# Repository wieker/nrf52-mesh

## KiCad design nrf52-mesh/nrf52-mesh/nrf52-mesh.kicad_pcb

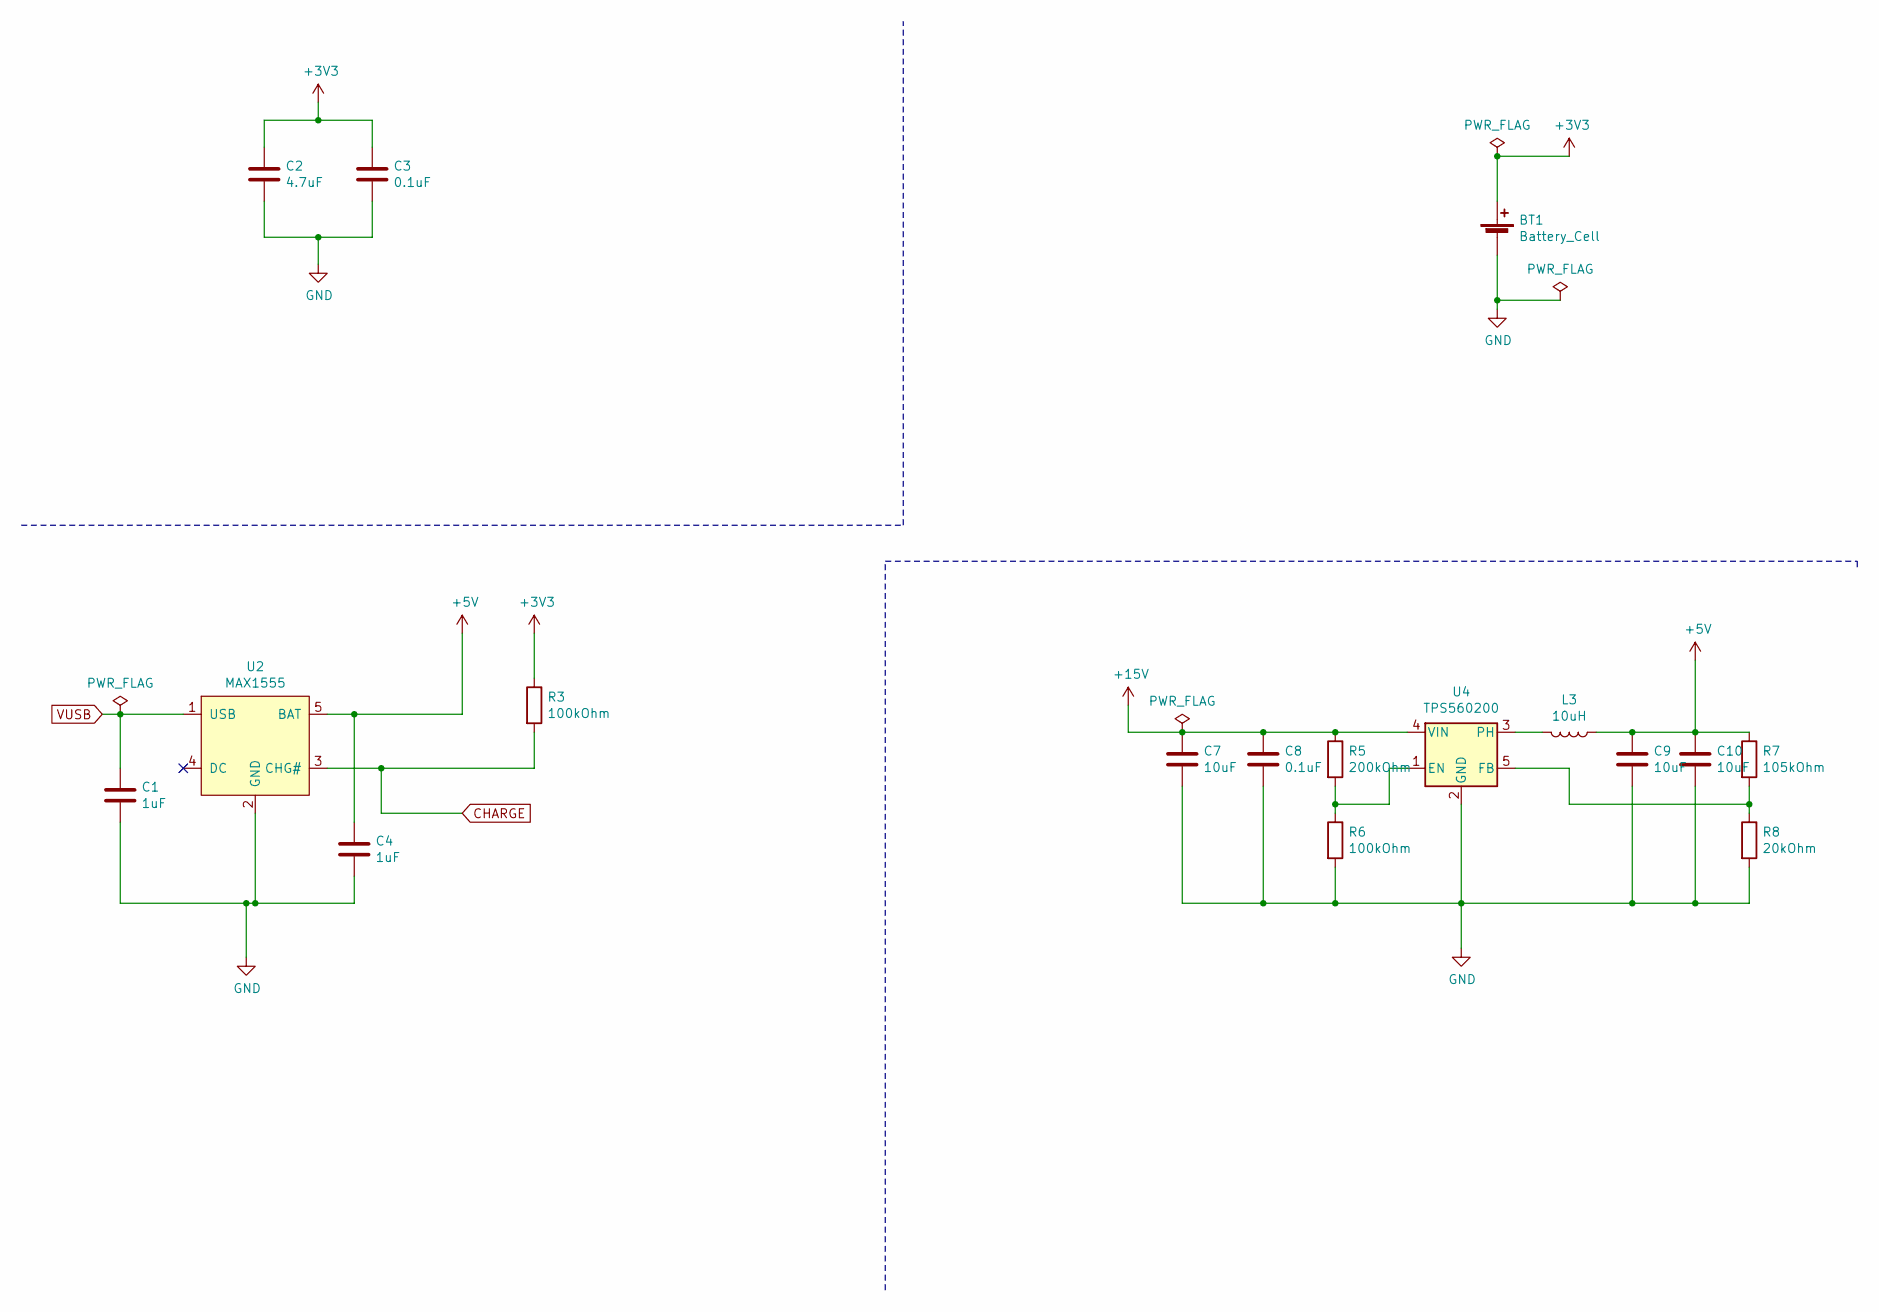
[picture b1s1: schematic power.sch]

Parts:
BT1: Battery_Cell; CR2032
C1, C4: 1uF; C_0402_1005Metric
C2: 4.7uF; C_0402_1005Metric
C3, C8: 0.1uF; C_0402_1005Metric
C7, C9, C10: 10uF; C_0603_1608Metric
L3: 10uH; L_0805_2012Metric
R3, R6: 100kOhm; R_0402_1005Metric
R5: 200kOhm; R_0402_1005Metric
R7: 105kOhm; R_0402_1005Metric
R8: 20kOhm; R_0402_1005Metric
U2: MAX1555; SOT-23-5
U4: TPS560200; SOT-23-5

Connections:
+3V3: BT1.1 (+), C2.1, C3.1, R3.1; also elsewhere on the board
+5V: C4.2, C9.1, C10.1, L3.1, R7.1, U2.5 (BAT); also elsewhere on the board
+15V: C7.1, C8.1, R5.1, U4.4 (VIN); also elsewhere on the board
CHARGE: R3.2, U2.3 (CHG#); also elsewhere on the board
GND: BT1.2 (-), C1.2, C2.2, C3.2, C4.1, C7.2, C8.2, C9.2, C10.2, R6.2, R8.2, U2.2 (GND), U4.2 (GND); also elsewhere on the board
unnamed: L3.2, U4.3 (PH)
unnamed: R5.2, R6.1, U4.1 (EN)
unnamed: R7.2, R8.1, U4.5 (FB)
VUSB: C1.1, U2.1 (USB); also elsewhere on the board

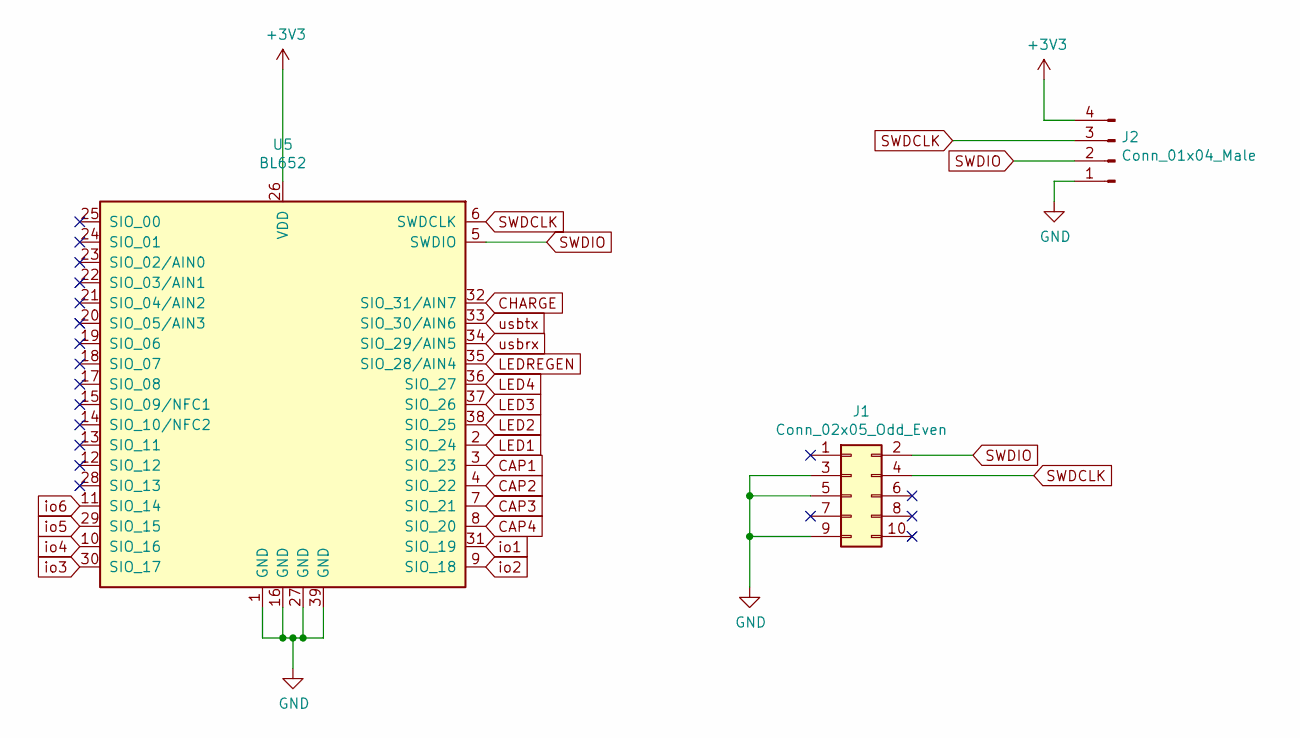
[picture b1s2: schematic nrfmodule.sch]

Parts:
J1: Conn_02x05_Odd_Even; PinSocket_2x05_P1.27mm_Vertical
J2: Conn_01x04_Male; PinHeader_1x04_P2.54mm_Vertical
U5: BL652; Laird_BL652

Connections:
+3V3: J2.4, U5.26 (VDD); also elsewhere on the board
CAP1: U5.3 (SIO_23); also elsewhere on the board
CAP2: U5.4 (SIO_22); also elsewhere on the board
CAP3: U5.7 (SIO_21); also elsewhere on the board
CAP4: U5.8 (SIO_20); also elsewhere on the board
CHARGE: U5.32 (SIO_31/AIN7); also elsewhere on the board
GND: J1.3, J1.5, J1.9, J2.1, U5.1 (GND), U5.16 (GND), U5.27 (GND), U5.39 (GND); also elsewhere on the board
LED1: U5.2 (SIO_24); also elsewhere on the board
LED2: U5.38 (SIO_25); also elsewhere on the board
LED3: U5.37 (SIO_26); also elsewhere on the board
LED4: U5.36 (SIO_27); also elsewhere on the board
LEDREGEN: U5.35 (SIO_28/AIN4); also elsewhere on the board
SWDCLK: J1.4, J2.3, U5.6 (SWDCLK)
SWDIO: J1.2, J2.2, U5.5 (SWDIO)
io1: U5.31 (SIO_19); also elsewhere on the board
io2: U5.9 (SIO_18); also elsewhere on the board
io3: U5.30 (SIO_17); also elsewhere on the board
io4: U5.10 (SIO_16); also elsewhere on the board
io5: U5.29 (SIO_15); also elsewhere on the board
io6: U5.11 (SIO_14); also elsewhere on the board
usbrx: U5.34 (SIO_29/AIN5); also elsewhere on the board
usbtx: U5.33 (SIO_30/AIN6); also elsewhere on the board

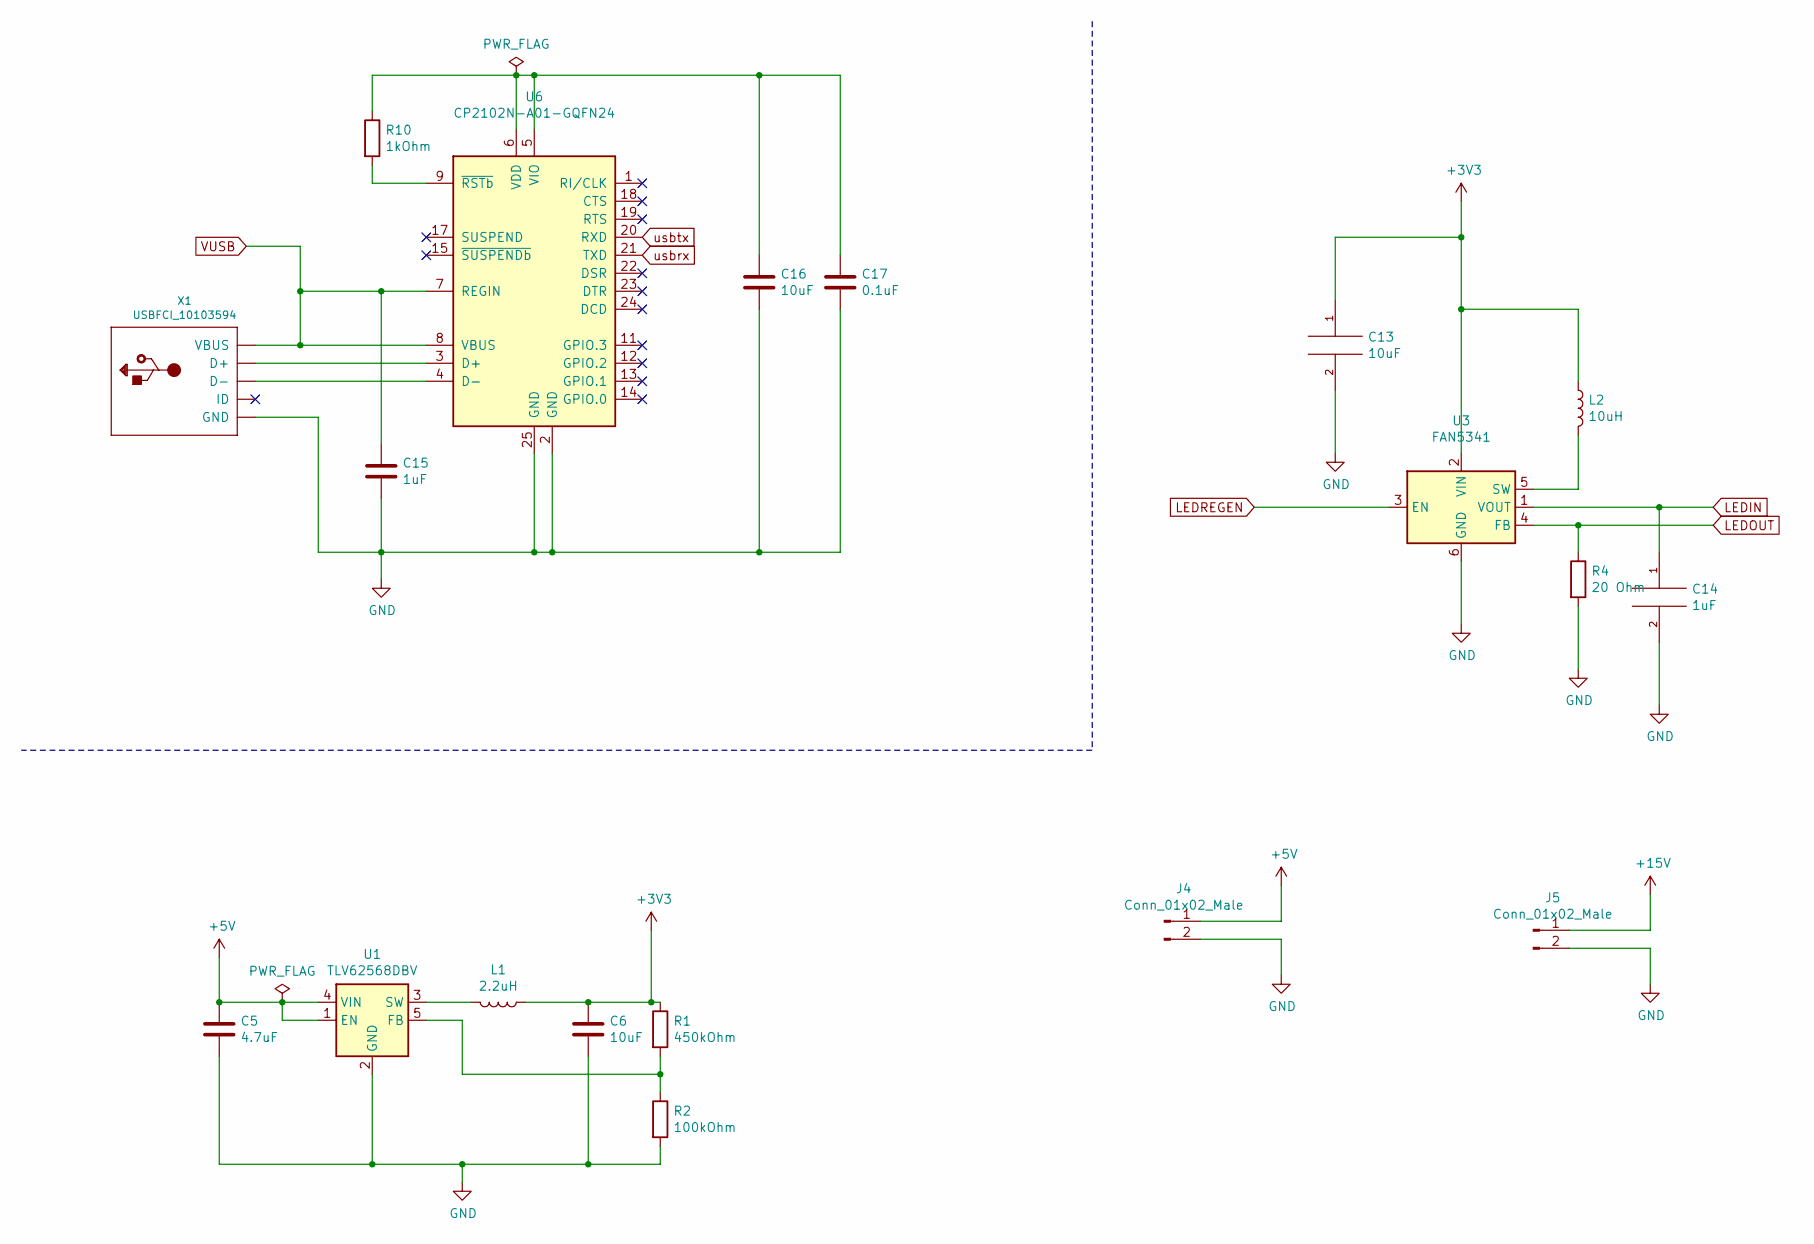
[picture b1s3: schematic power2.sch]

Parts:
C5: 4.7uF; C_0402_1005Metric
C6: 10uF; C_0402_1005Metric
C13, C16: 10uF; C_0603_1608Metric
C14, C15: 1uF; C_0402_1005Metric
C17: 0.1uF; C_0402_1005Metric
J4, J5: Conn_01x02_Male; PinHeader_1x02_P2.54mm_Vertical
L1: 2.2uH; L_0805_2012Metric
L2: 10uH; L_0805_2012Metric
R1: 450kOhm; R_0402_1005Metric
R2: 100kOhm; R_0402_1005Metric
R4: 20 Ohm; R_0402_1005Metric
R10: 1kOhm; R_0402_1005Metric
U1: TLV62568DBV; SOT-23-5
U3: FAN5341
U6: CP2102N-A01-GQFN24; QFN-24-1EP_4x4mm_P0.5mm_EP2.6x2.6mm
X1: USBFCI_10103594; FCI_10103594_MILL

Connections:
+3V3: C6.1, C13.1, L1.1, L2.1, R1.1, U3.2 (VIN); also elsewhere on the board
+5V: C5.1, J4.1, U1.1 (EN), U1.4 (VIN); also elsewhere on the board
+15V: J5.1; also elsewhere on the board
GND: C5.2, C6.2, C13.2, C14.2, C15.2, C16.2, C17.2, J4.2, J5.2, R2.2, R4.2, U1.2 (GND), U3.6 (GND), U6.2 (GND), U6.25 (GND), X1.BASE@1 (GND), X1.BASE@2 (GND), X1.GND, X1.SPRT@1 (GND), X1.SPRT@2 (GND), X1.SPRT@3 (GND), X1.SPRT@4 (GND); also elsewhere on the board
LEDIN: C14.1, U3.1 (VOUT); also elsewhere on the board
LEDOUT: R4.1, U3.4 (FB); also elsewhere on the board
LEDREGEN: U3.3 (EN); also elsewhere on the board
unnamed: C16.1, C17.1, R10.1, U6.5 (VIO), U6.6 (VDD)
unnamed: L1.2, U1.3 (SW)
unnamed: L2.2, U3.5 (SW)
unnamed: R1.2, R2.1, U1.5 (FB)
unnamed: R10.2, U6.9 (~RSTb)
unnamed: U6.3 (D+), X1.D+
unnamed: U6.4 (D-), X1.D-
VUSB: C15.1, U6.7 (REGIN), U6.8 (VBUS), X1.VBUS; also elsewhere on the board
usbrx: U6.21 (TXD); also elsewhere on the board
usbtx: U6.20 (RXD); also elsewhere on the board

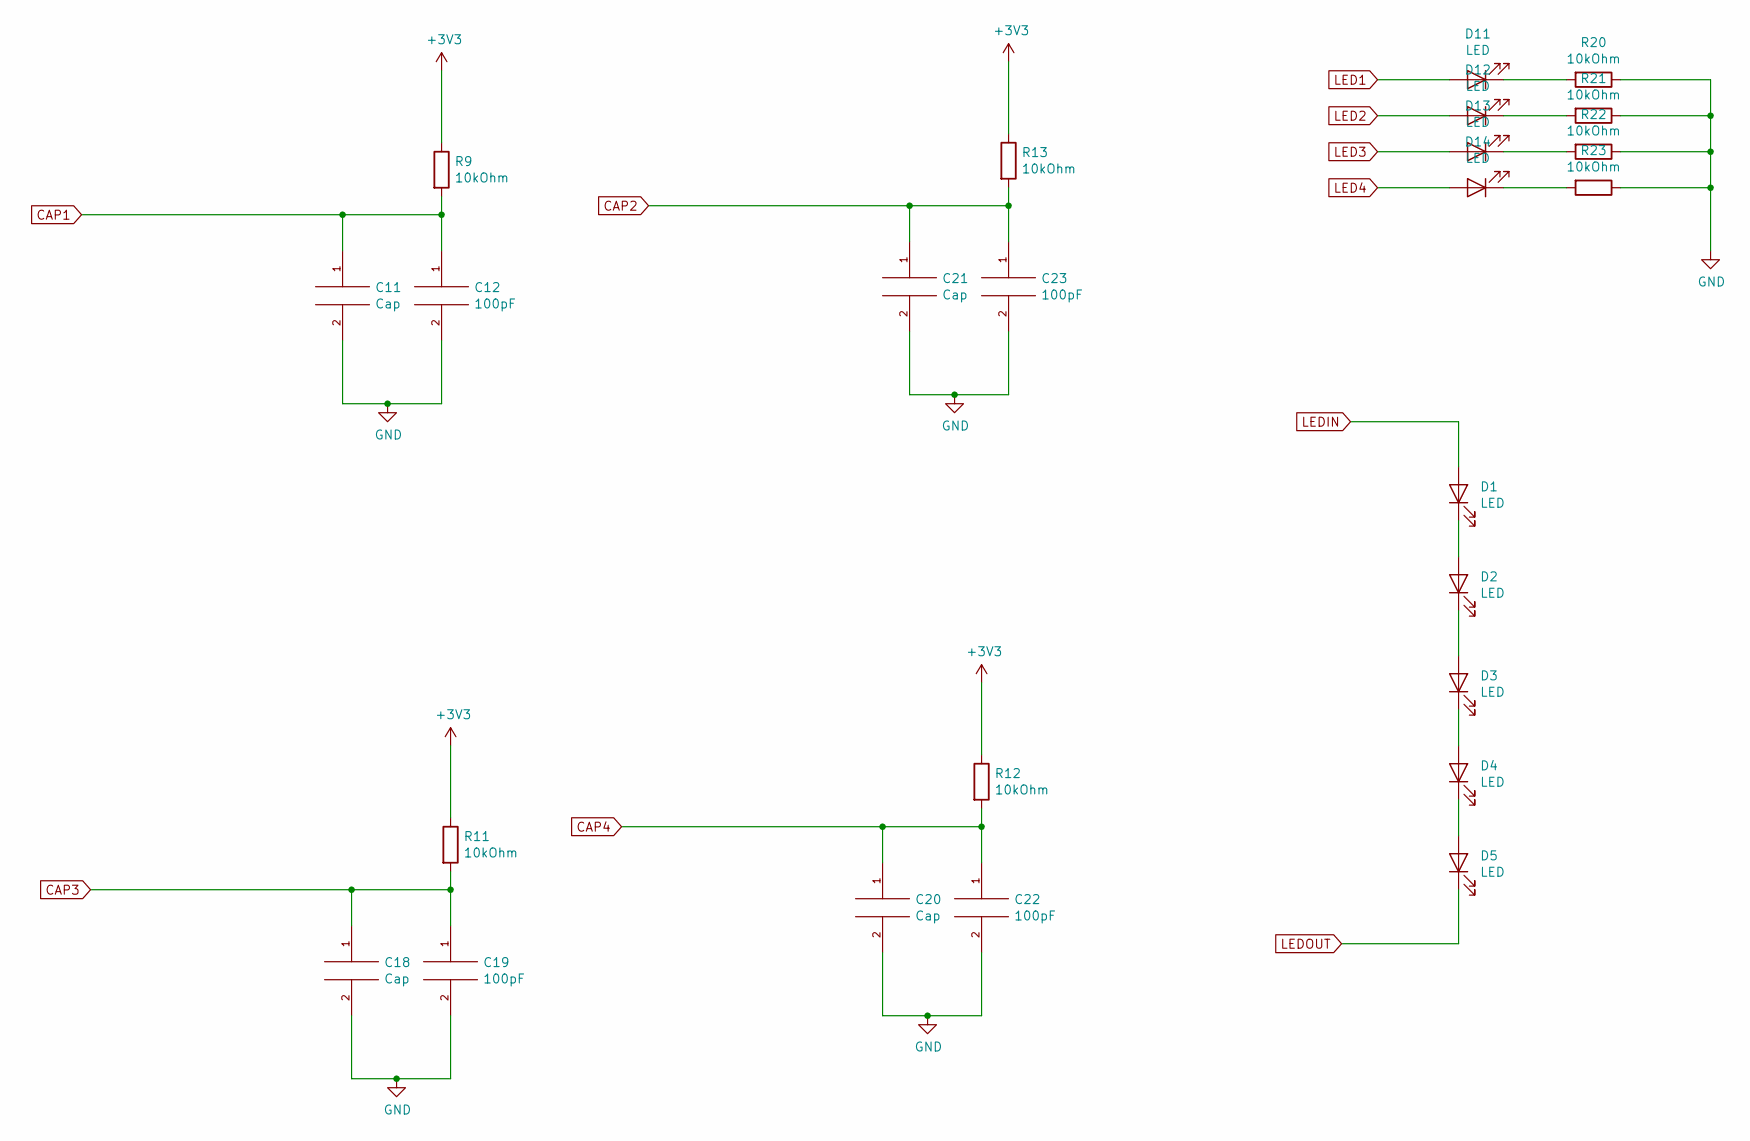
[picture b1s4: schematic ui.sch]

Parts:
C11, C18, C20, C21: Cap; CAPBUTTON
C12, C19, C22, C23: 100pF; C_0402_1005Metric
D1, D2, D3, D4, D5, D11, D12, D13, D14: LED; LED_1206_3216Metric
R9, R11, R12, R13, R20, R21, R22, R23: 10kOhm; R_0402_1005Metric

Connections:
+3V3: R9.1, R11.1, R12.1, R13.1; also elsewhere on the board
CAP1: C11.1, C12.1, R9.2; also elsewhere on the board
CAP2: C21.1, C23.1, R13.2; also elsewhere on the board
CAP3: C18.1, C19.1, R11.2; also elsewhere on the board
CAP4: C20.1, C22.1, R12.2; also elsewhere on the board
GND: C11.2, C12.2, C18.2, C19.2, C20.2, C21.2, C22.2, C23.2, R20.1, R21.1, R22.1, R23.1; also elsewhere on the board
LED1: D11.2 (A); also elsewhere on the board
LED2: D12.2 (A); also elsewhere on the board
LED3: D13.2 (A); also elsewhere on the board
LED4: D14.2 (A); also elsewhere on the board
LEDIN: D1.2 (A); also elsewhere on the board
LEDOUT: D5.1 (K); also elsewhere on the board
unnamed: D1.1 (K), D2.2 (A)
unnamed: D2.1 (K), D3.2 (A)
unnamed: D3.1 (K), D4.2 (A)
unnamed: D4.1 (K), D5.2 (A)
unnamed: D11.1 (K), R20.2
unnamed: D12.1 (K), R21.2
unnamed: D13.1 (K), R22.2
unnamed: D14.1 (K), R23.2

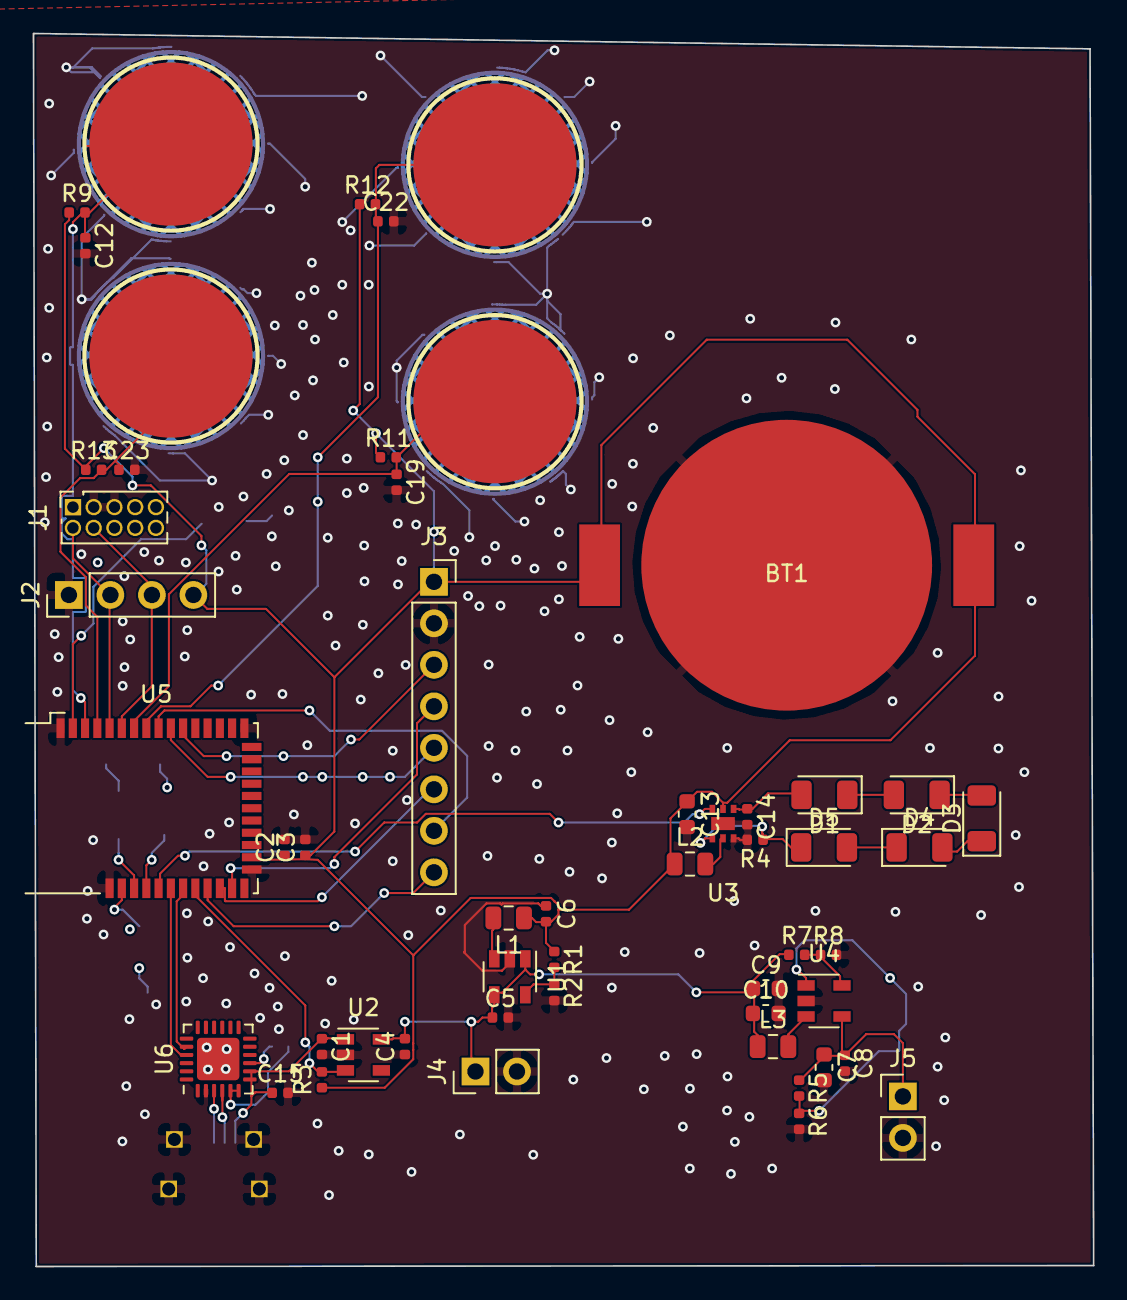
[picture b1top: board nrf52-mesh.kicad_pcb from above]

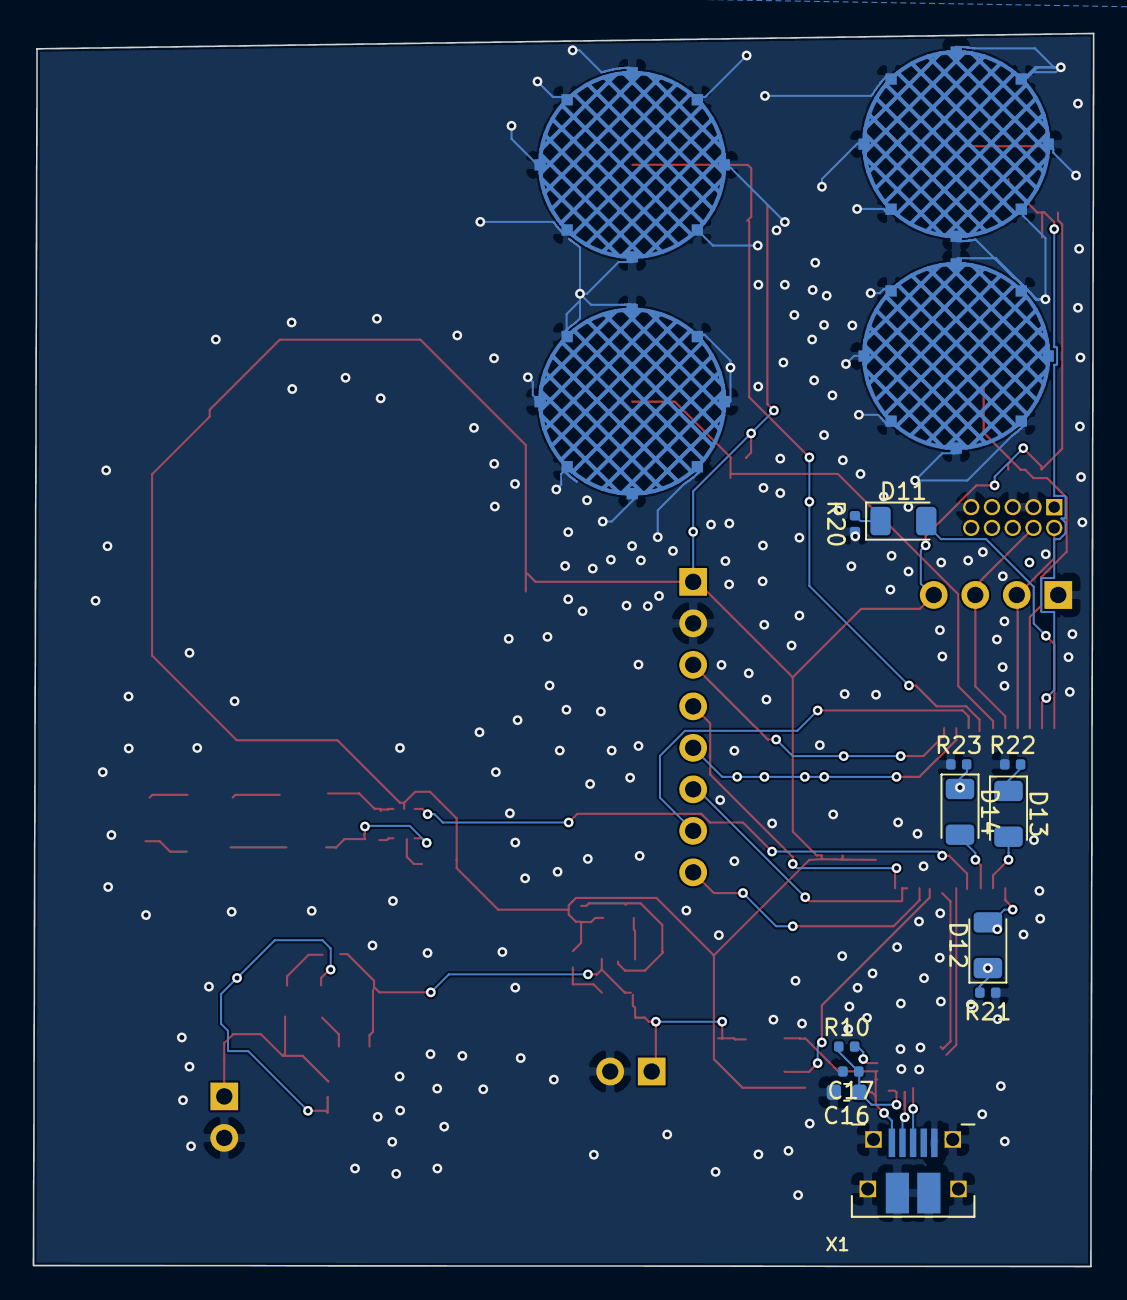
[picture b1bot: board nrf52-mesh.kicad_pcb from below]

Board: 2 copper layers, 64.9 x 75.5 mm, 65 parts (12 on the bottom side), 45 nets.

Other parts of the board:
J3: Conn_01x08; PinSocket_1x08_P2.54mm_Vertical

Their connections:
+3V3: J3.1; also elsewhere on the board
GND: J3.2; also elsewhere on the board
io1: J3.8; also elsewhere on the board
io2: J3.7; also elsewhere on the board
io3: J3.6; also elsewhere on the board
io4: J3.5; also elsewhere on the board
io5: J3.4; also elsewhere on the board
io6: J3.3; also elsewhere on the board

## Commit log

2020-02-13 nRF52 mesh board init
2020-02-18 power for nrf52
2020-02-20 continue nRF52 power
2020-02-24 more
2020-02-25 next portion
2020-02-26 CP2102N + MAX1555 + FAN5341 + TPS560200 + TLV62568
2020-04-06 nRF52 + ESP WROOM
